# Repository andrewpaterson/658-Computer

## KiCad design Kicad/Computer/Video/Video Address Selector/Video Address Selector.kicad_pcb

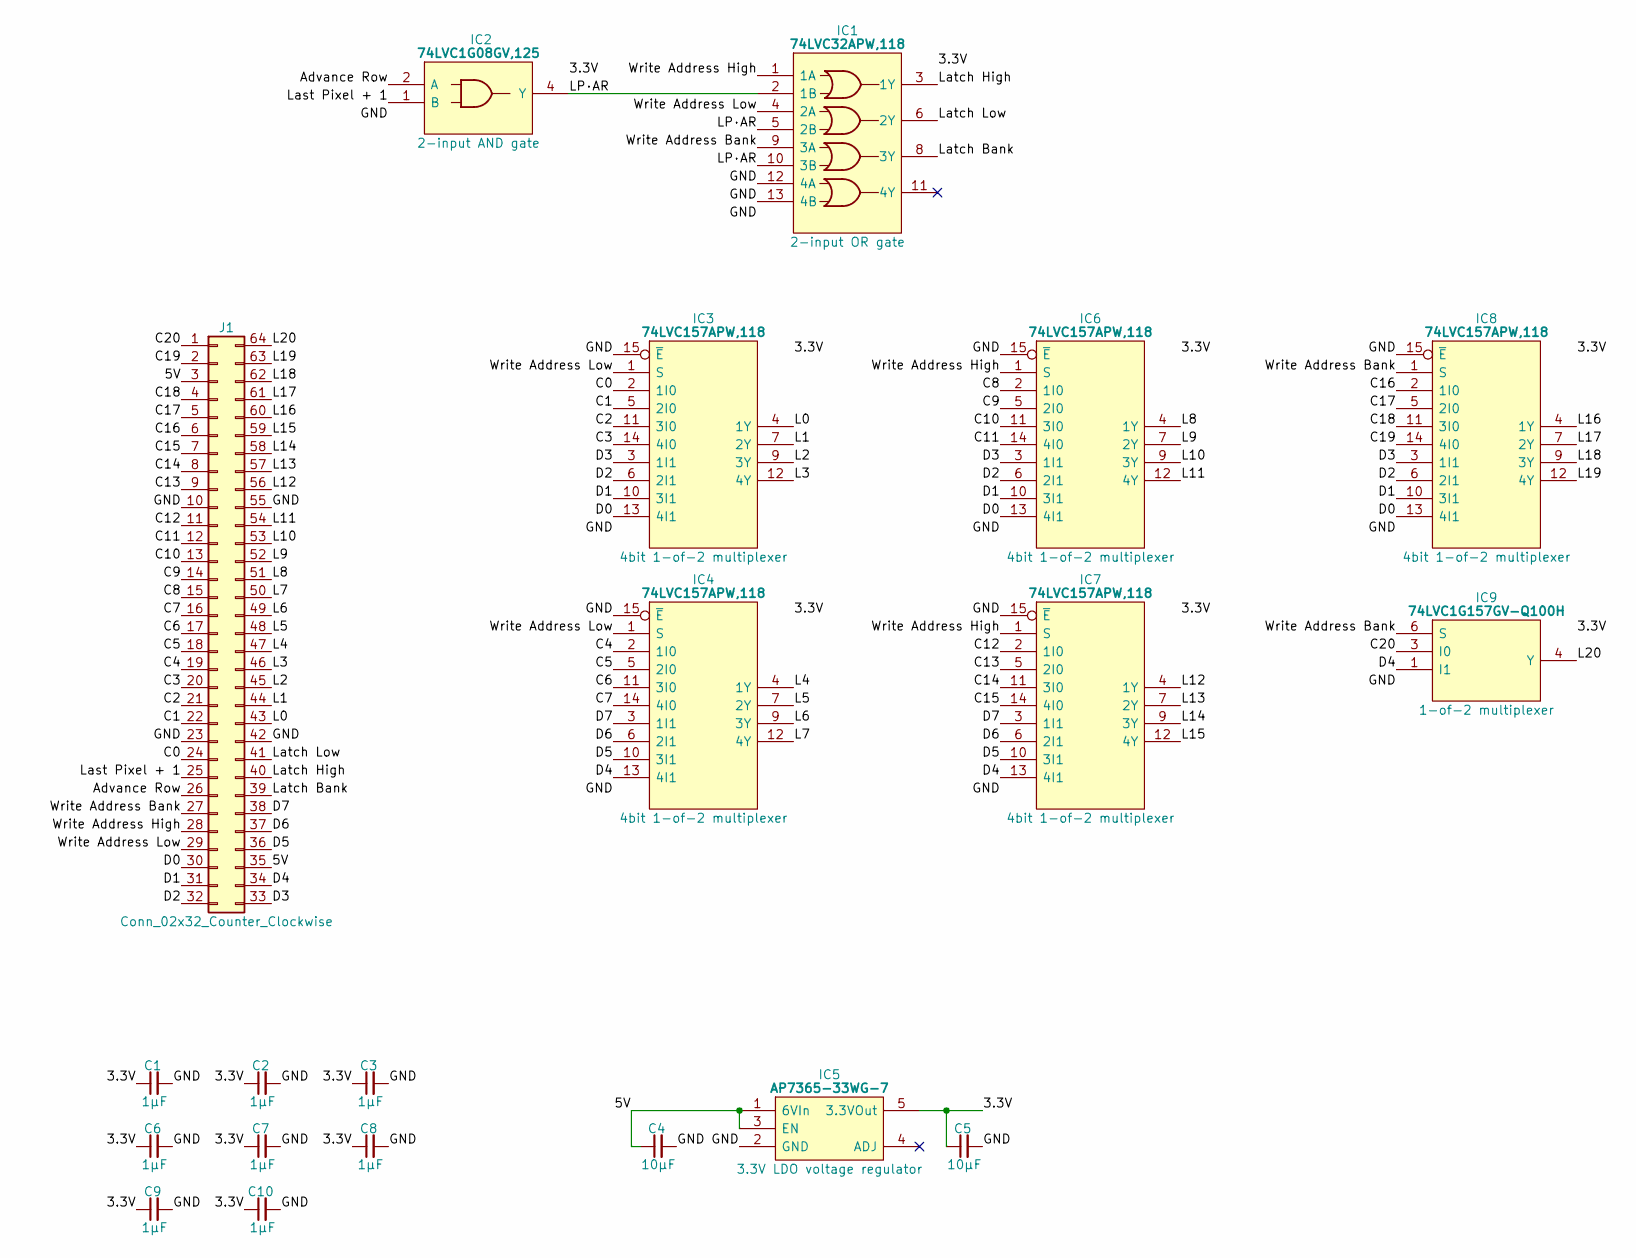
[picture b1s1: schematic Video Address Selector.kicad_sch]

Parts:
C1, C2, C3, C6, C7, C8, C9, C10: 1μF; C_0805
C4, C5: 10µF; C_0805
IC1: 74LVC32APW,118; SOP65P640X110-14N; Manufacturer_Part_Number 74LVC32APW,118; Mouser Part Number 771-74LVC32APW-T
IC2: 74LVC1G08GV,125; SOT95P275X110-5N; Manufacturer_Part_Number 74LVC1G08GV,125; Mouser Part Number 771-74LVC1G08GV
IC3, IC4, IC6, IC7, IC8: 74LVC157APW,118; SOP65P640X110-16N; Mouser Part Number 771-74LVC157APW-T
IC5: AP7365-33WG-7; SOT95P285X130-5N; Manufacturer_Part_Number AP7365-33WG-7; Mouser Part Number 621-AP7365-33WG-7
IC9: 74LVC1G157GV-Q100H; SOT95P275X110-6N; Manufacturer_Part_Number 74LVC1G157GV-Q100H; Mouser Part Number 771-74LVC1G157GVQ100
J1: Conn_02x32_Counter_Clockwise; DIP-64_Board_W15.24mm

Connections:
/3.3V: C1.1, C2.1, C3.1, C5.1, C6.1, C7.1, C8.1, C9.1, C10.1, IC1.14 (3V), IC2.5 (3V), IC3.16 (3V), IC4.16 (3V), IC5.5 (3.3VOut), IC6.16 (3V), IC7.16 (3V), IC8.16 (3V), IC9.5 (3V)
/5V: C4.1, IC5.1 (6VIn), IC5.3 (EN), J1.3, J1.35
/Advance Row: IC2.2 (A), J1.26
/C0: IC3.2 (1I0), J1.24
/C1: IC3.5 (2I0), J1.22
/C2: IC3.11 (3I0), J1.21
/C3: IC3.14 (4I0), J1.20
/C4: IC4.2 (1I0), J1.19
/C5: IC4.5 (2I0), J1.18
/C6: IC4.11 (3I0), J1.17
/C7: IC4.14 (4I0), J1.16
/C8: IC6.2 (1I0), J1.15
/C9: IC6.5 (2I0), J1.14
/C10: IC6.11 (3I0), J1.13
/C11: IC6.14 (4I0), J1.12
/C12: IC7.2 (1I0), J1.11
/C13: IC7.5 (2I0), J1.9
/C14: IC7.11 (3I0), J1.8
/C15: IC7.14 (4I0), J1.7
/C16: IC8.2 (1I0), J1.6
/C17: IC8.5 (2I0), J1.5
/C18: IC8.11 (3I0), J1.4
/C19: IC8.14 (4I0), J1.2
/C20: IC9.3 (I0), J1.1
/D0: IC3.13 (4I1), IC6.13 (4I1), IC8.13 (4I1), J1.30
/D1: IC3.10 (3I1), IC6.10 (3I1), IC8.10 (3I1), J1.31
/D2: IC3.6 (2I1), IC6.6 (2I1), IC8.6 (2I1), J1.32
/D3: IC3.3 (1I1), IC6.3 (1I1), IC8.3 (1I1), J1.33
/D4: IC4.13 (4I1), IC7.13 (4I1), IC9.1 (I1), J1.34
/D5: IC4.10 (3I1), IC7.10 (3I1), J1.36
/D6: IC4.6 (2I1), IC7.6 (2I1), J1.37
/D7: IC4.3 (1I1), IC7.3 (1I1), J1.38
/GND: C1.2, C2.2, C3.2, C4.2, C5.2, C6.2, C7.2, C8.2, C9.2, C10.2, IC1.7 (GND), IC1.12 (4A), IC1.13 (4B), IC2.3 (GND), IC3.8 (GND), IC3.15 (~E), IC4.8 (GND), IC4.15 (~E), IC5.2 (GND), IC6.8 (GND), IC6.15 (~E), IC7.8 (GND), IC7.15 (~E), IC8.8 (GND), IC8.15 (~E), IC9.2 (GND), J1.10, J1.23, J1.42, J1.55
/L0: IC3.4 (1Y), J1.43
/L1: IC3.7 (2Y), J1.44
/L2: IC3.9 (3Y), J1.45
/L3: IC3.12 (4Y), J1.46
/L4: IC4.4 (1Y), J1.47
/L5: IC4.7 (2Y), J1.48
/L6: IC4.9 (3Y), J1.49
/L7: IC4.12 (4Y), J1.50
/L8: IC6.4 (1Y), J1.51
/L9: IC6.7 (2Y), J1.52
/L10: IC6.9 (3Y), J1.53
/L11: IC6.12 (4Y), J1.54
/L12: IC7.4 (1Y), J1.56
/L13: IC7.7 (2Y), J1.57
/L14: IC7.9 (3Y), J1.58
/L15: IC7.12 (4Y), J1.59
/L16: IC8.4 (1Y), J1.60
/L17: IC8.7 (2Y), J1.61
/L18: IC8.9 (3Y), J1.62
/L19: IC8.12 (4Y), J1.63
/L20: IC9.4 (Y), J1.64
/LP·AR: IC1.2 (1B), IC1.5 (2B), IC1.10 (3B), IC2.4 (Y)
/Last Pixel + 1: IC2.1 (B), J1.25
/Latch Bank: IC1.8 (3Y), J1.39
/Latch High: IC1.3 (1Y), J1.40
/Latch Low: IC1.6 (2Y), J1.41
/Write Address Bank: IC1.9 (3A), IC8.1 (S), IC9.6 (S), J1.27
/Write Address High: IC1.1 (1A), IC6.1 (S), IC7.1 (S), J1.28
/Write Address Low: IC1.4 (2A), IC3.1 (S), IC4.1 (S), J1.29

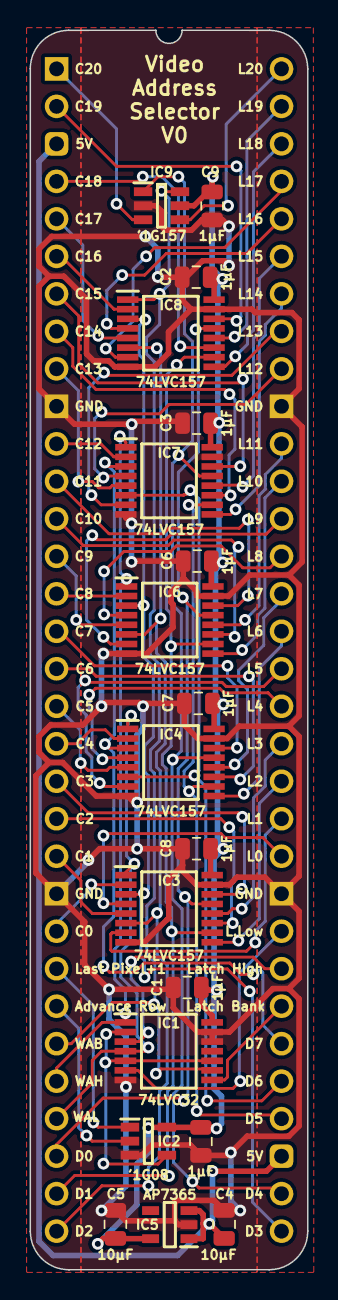
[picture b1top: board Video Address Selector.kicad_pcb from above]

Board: 2 copper layers, 18.8 x 84.0 mm, 20 parts (0 on the bottom side), 62 nets.

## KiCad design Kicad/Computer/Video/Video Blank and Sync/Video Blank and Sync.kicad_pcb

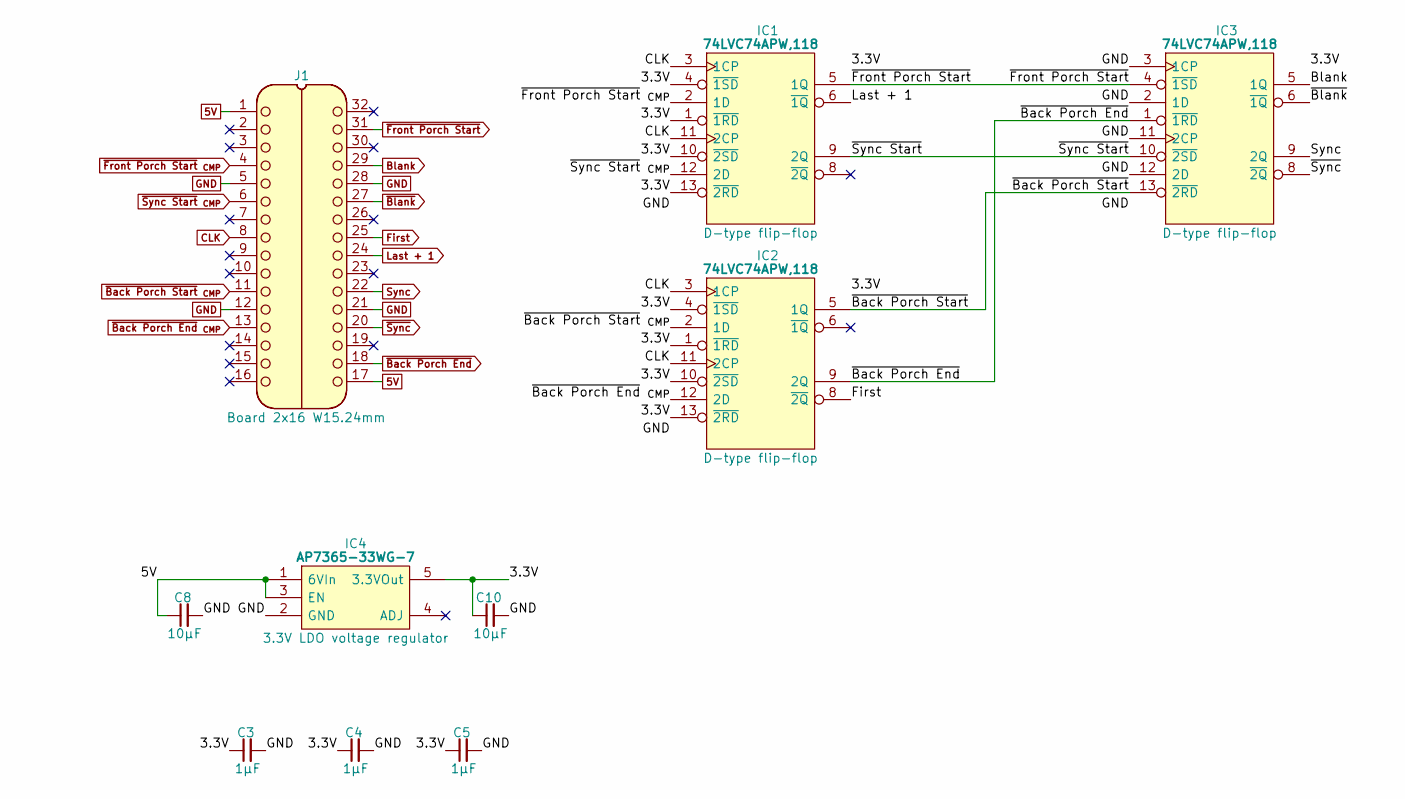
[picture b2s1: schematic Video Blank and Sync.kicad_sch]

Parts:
C3, C4, C5: 1μF; C_0805
C8, C10: 10µF; C_0805
IC1, IC2, IC3: 74LVC74APW,118; SOP65P640X110-14N; Mouser Part Number 771-74LVC74APW-T
IC4: AP7365-33WG-7; SOT95P285X130-5N; Manufacturer_Part_Number AP7365-33WG-7; Mouser Part Number 621-AP7365-33WG-7
J1: Board 2x16 W15.24mm; DIP-32_Board_W15.24mm

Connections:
5V: C8.1, IC4.1 (6VIn), IC4.3 (EN), J1.1, J1.17
/3.3V: C3.1, C4.1, C5.1, C10.1, IC1.1 (~1RD), IC1.4 (~1SD), IC1.10 (~2SD), IC1.13 (~2RD), IC1.14 (3V), IC2.1 (~1RD), IC2.4 (~1SD), IC2.10 (~2SD), IC2.13 (~2RD), IC2.14 (3V), IC3.14 (3V), IC4.5 (3.3VOut)
/~Back Porch Start: IC2.5 (1Q), IC3.13 (~2RD)
/~Sync Start: IC1.9 (2Q), IC3.10 (~2SD)
Blank: IC3.5 (1Q), J1.29
CLK: IC1.3 (1CP), IC1.11 (2CP), IC2.3 (1CP), IC2.11 (2CP), J1.8
First: IC2.8 (~2Q), J1.25
GND: C3.2, C4.2, C5.2, C8.2, C10.2, IC1.7 (GND), IC2.7 (GND), IC3.2 (1D), IC3.3 (1CP), IC3.7 (GND), IC3.11 (2CP), IC3.12 (2D), IC4.2 (GND), J1.5, J1.12, J1.21, J1.28
Last + 1: IC1.6 (~1Q), J1.24
Sync: IC3.9 (2Q), J1.22
~Back Porch End: IC2.9 (2Q), IC3.1 (~1RD), J1.18
~Back Porch End _{CMP}: IC2.12 (2D), J1.13
~Back Porch Start _{CMP}: IC2.2 (1D), J1.11
~Blank: IC3.6 (~1Q), J1.27
~Front Porch Start: IC1.5 (1Q), IC3.4 (~1SD), J1.31
~Front Porch Start _{CMP}: IC1.2 (1D), J1.4
~Sync Start _{CMP}: IC1.12 (2D), J1.6
~Sync: IC3.8 (~2Q), J1.20

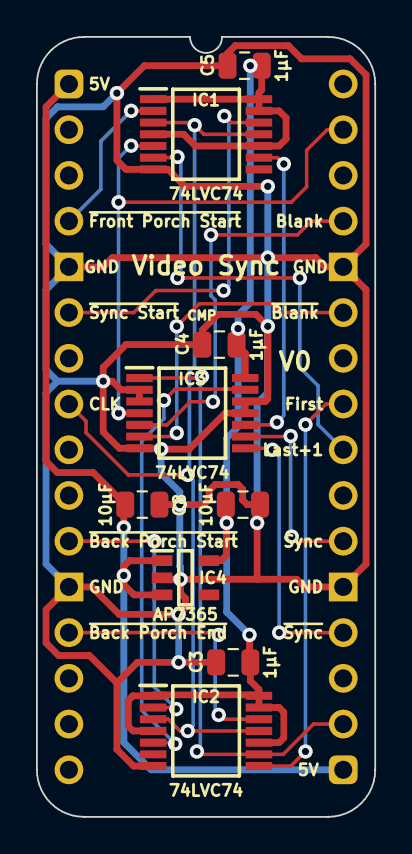
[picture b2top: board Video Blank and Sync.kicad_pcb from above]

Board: 2 copper layers, 18.8 x 43.3 mm, 10 parts (0 on the bottom side), 18 nets.

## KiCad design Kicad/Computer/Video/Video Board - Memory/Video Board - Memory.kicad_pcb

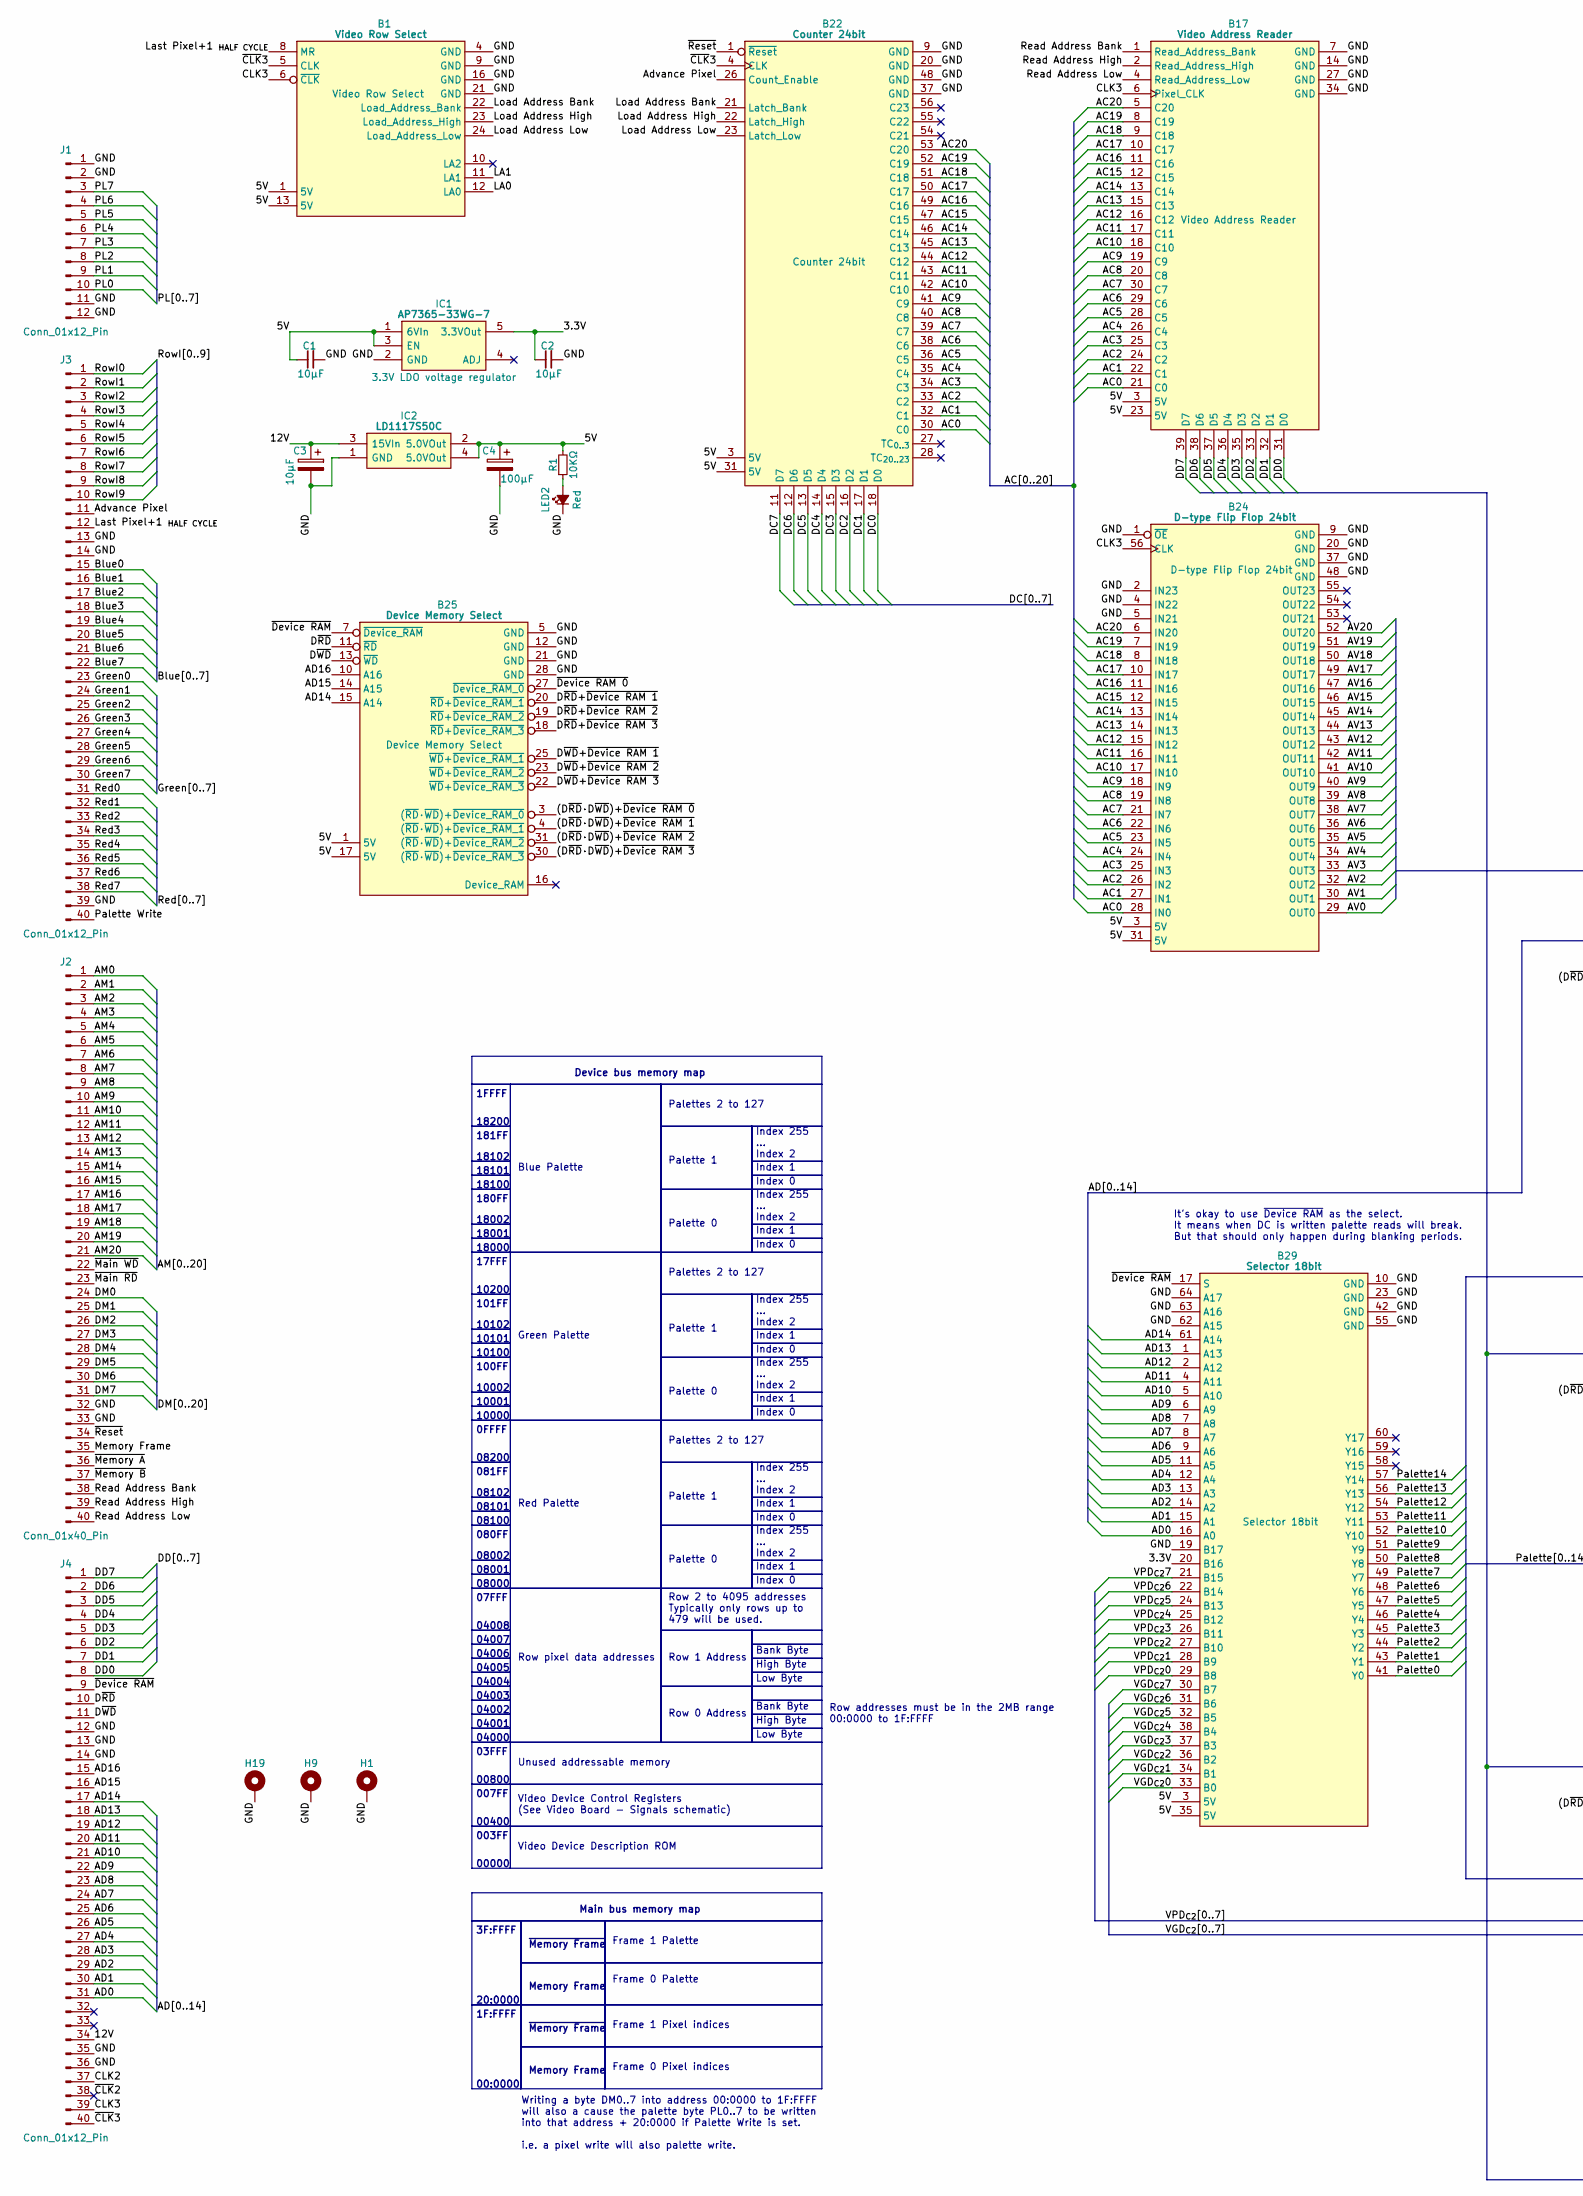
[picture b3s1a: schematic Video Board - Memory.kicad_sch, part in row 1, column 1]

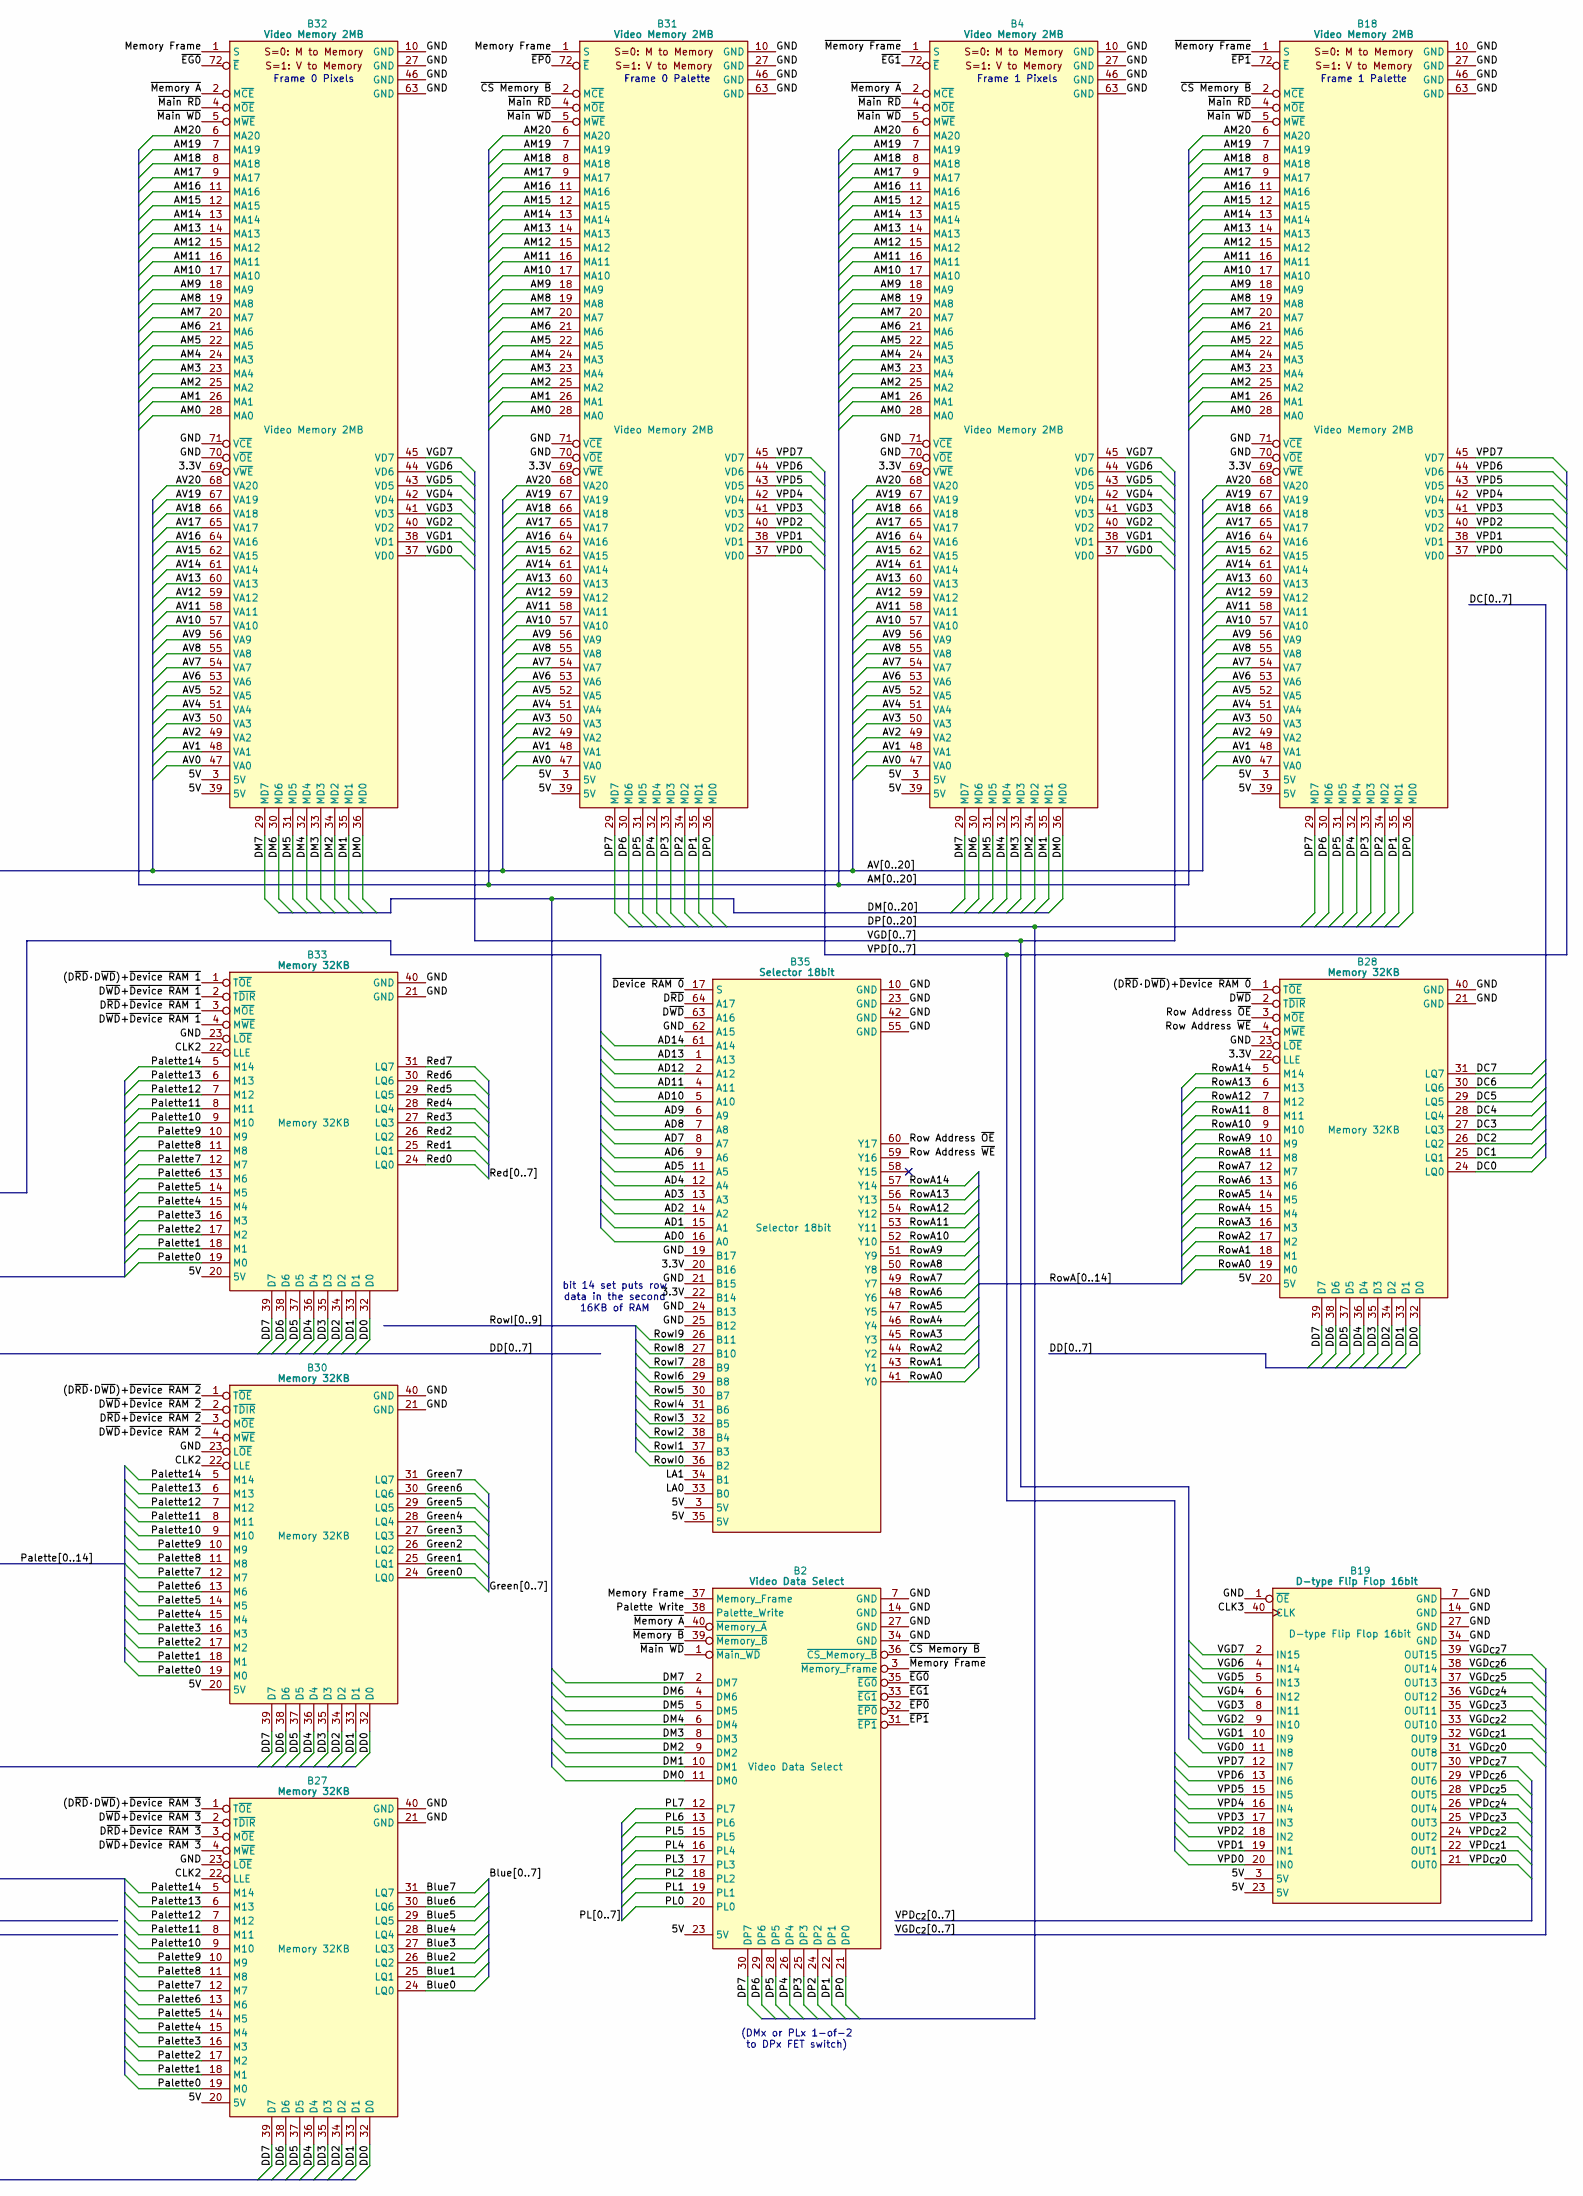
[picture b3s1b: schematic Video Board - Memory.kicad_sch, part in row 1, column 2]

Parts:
B1: Video Row Select; HCP65_Video_Row_Select
B2: Video Data Select; HCP65_Video_Data_Select
B4, B18, B31, B32: Video Memory 2MB; HCP65_Video_Memory_2MB
B17: Video Address Reader; HCP65_Video_Address_Reader
B19: D-type Flip Flop 16bit; HCP65_D_Flip_Flop_16bit
B22: Counter 24bit; HCP65_Counter_24bit
B24: D-type Flip Flop 24bit; HCP65_D_Flip_Flop_24bit
B25: Device Memory Select; HCP65_Video_Device_RAM_Select
B27, B28, B30, B33: Memory 32KB; HCP65_Memory_32KB_With_Latch
B29, B35: Selector 18bit; HCP65_Selector_18bit
C1, C2: 10µF; C_0805
C3: 10μF; CP_Radial_D4.0mm_P2.00mm
C4: 100μF; CP_Radial_D4.0mm_P2.00mm
H1, H9, H19: MountingHole_Pad; HCP65_MountingHole_M3_
IC1: AP7365-33WG-7; SOT95P285X130-5N; Manufacturer_Part_Number AP7365-33WG-7; Mouser Part Number 621-AP7365-33WG-7
IC2: LD1117S50C; LD1117S33C; Manufacturer_Part_Number LD1117S50C
J1: Conn_01x12_Pin; PinSocket_2x06_P2.54mm_Vertical
J2: Conn_01x40_Pin; PinSocket_2x20_P2.54mm_Vertical
J3, J4: Conn_01x12_Pin; PinSocket_2x20_P2.54mm_Vertical
LED2: Red; LED_D5.0mm
R1: 10KΩ; R_0805

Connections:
/3.3V: B4.69 (V~WE), B18.69 (V~WE), B28.22 (LLE), B29.20 (B16), B31.69 (V~WE), B32.69 (V~WE), B35.20 (B16), B35.22 (B14), C2.1, IC1.5 (3.3VOut)
/5V: B1.1 (5V), B1.13 (5V), B2.23 (5V), B4.3 (5V), B4.39 (5V), B17.3 (5V), B17.23 (5V), B18.3 (5V), B18.39 (5V), B19.3 (5V), B19.23 (5V), B22.3 (5V), B22.31 (5V), B24.3 (5V), B24.31 (5V), B25.1 (5V), B25.17 (5V), B27.20 (5V), B28.20 (5V), B29.3 (5V), B29.35 (5V), B30.20 (5V), B31.3 (5V), B31.39 (5V), B32.3 (5V), B32.39 (5V), B33.20 (5V), B35.3 (5V), B35.35 (5V), C1.1, C4.1, IC1.1 (6VIn), IC1.3 (EN), IC2.2 (5.0VOut), IC2.4 (5.0VOut), R1.2
/12V: C3.1, IC2.3 (15VIn), J4.34
/(D~RD·D~WD)+~Device RAM 0: B25.3 ((~RD·~WD)+~Device_RAM_0), B28.1 (T~OE)
/(D~RD·D~WD)+~Device RAM 1: B25.4 ((~RD·~WD)+~Device_RAM_1), B33.1 (T~OE)
/(D~RD·D~WD)+~Device RAM 2: B25.31 ((~RD·~WD)+~Device_RAM_2), B30.1 (T~OE)
/(D~RD·D~WD)+~Device RAM 3: B25.30 ((~RD·~WD)+~Device_RAM_3), B27.1 (T~OE)
/AC0: B17.21 (C0), B22.30 (C0), B24.28 (IN0)
/AC1: B17.22 (C1), B22.32 (C1), B24.27 (IN1)
/AC2: B17.24 (C2), B22.33 (C2), B24.26 (IN2)
/AC3: B17.25 (C3), B22.34 (C3), B24.25 (IN3)
/AC4: B17.26 (C4), B22.35 (C4), B24.24 (IN4)
/AC5: B17.28 (C5), B22.36 (C5), B24.23 (IN5)
/AC6: B17.29 (C6), B22.38 (C6), B24.22 (IN6)
/AC7: B17.30 (C7), B22.39 (C7), B24.21 (IN7)
/AC8: B17.20 (C8), B22.40 (C8), B24.19 (IN8)
/AC9: B17.19 (C9), B22.41 (C9), B24.18 (IN9)
/AC10: B17.18 (C10), B22.42 (C10), B24.17 (IN10)
/AC11: B17.17 (C11), B22.43 (C11), B24.16 (IN11)
/AC12: B17.16 (C12), B22.44 (C12), B24.15 (IN12)
/AC13: B17.15 (C13), B22.45 (C13), B24.14 (IN13)
/AC14: B17.13 (C14), B22.46 (C14), B24.13 (IN14)
/AC15: B17.12 (C15), B22.47 (C15), B24.12 (IN15)
/AC16: B17.11 (C16), B22.49 (C16), B24.11 (IN16)
/AC17: B17.10 (C17), B22.50 (C17), B24.10 (IN17)
/AC18: B17.9 (C18), B22.51 (C18), B24.8 (IN18)
/AC19: B17.8 (C19), B22.52 (C19), B24.7 (IN19)
/AC20: B17.5 (C20), B22.53 (C20), B24.6 (IN20)
/AD0: B29.16 (A0), B35.16 (A0), J4.31
/AD1: B29.15 (A1), B35.15 (A1), J4.30
/AD2: B29.14 (A2), B35.14 (A2), J4.29
/AD3: B29.13 (A3), B35.13 (A3), J4.28
/AD4: B29.12 (A4), B35.12 (A4), J4.27
/AD5: B29.11 (A5), B35.11 (A5), J4.26
/AD6: B29.9 (A6), B35.9 (A6), J4.25
/AD7: B29.8 (A7), B35.8 (A7), J4.24
/AD8: B29.7 (A8), B35.7 (A8), J4.23
/AD9: B29.6 (A9), B35.6 (A9), J4.22
/AD10: B29.5 (A10), B35.5 (A10), J4.21
/AD11: B29.4 (A11), B35.4 (A11), J4.20
/AD12: B29.2 (A12), B35.2 (A12), J4.19
/AD13: B29.1 (A13), B35.1 (A13), J4.18
/AD14: B25.15 (A14), B29.61 (A14), B35.61 (A14), J4.17
/AD15: B25.14 (A15), J4.16
/AD16: B25.10 (A16), J4.15
/AM0: B4.28 (MA0), B18.28 (MA0), B31.28 (MA0), B32.28 (MA0), J2.1
/AM1: B4.26 (MA1), B18.26 (MA1), B31.26 (MA1), B32.26 (MA1), J2.2
/AM2: B4.25 (MA2), B18.25 (MA2), B31.25 (MA2), B32.25 (MA2), J2.3
/AM3: B4.23 (MA4), B18.23 (MA4), B31.23 (MA4), B32.23 (MA4), J2.4
/AM4: B4.24 (MA3), B18.24 (MA3), B31.24 (MA3), B32.24 (MA3), J2.5
/AM5: B4.22 (MA5), B18.22 (MA5), B31.22 (MA5), B32.22 (MA5), J2.6
/AM6: B4.21 (MA6), B18.21 (MA6), B31.21 (MA6), B32.21 (MA6), J2.7
/AM7: B4.20 (MA7), B18.20 (MA7), B31.20 (MA7), B32.20 (MA7), J2.8
/AM8: B4.19 (MA8), B18.19 (MA8), B31.19 (MA8), B32.19 (MA8), J2.9
/AM9: B4.18 (MA9), B18.18 (MA9), B31.18 (MA9), B32.18 (MA9), J2.10
/AM10: B4.17 (MA10), B18.17 (MA10), B31.17 (MA10), B32.17 (MA10), J2.11
/AM11: B4.16 (MA11), B18.16 (MA11), B31.16 (MA11), B32.16 (MA11), J2.12
/AM12: B4.15 (MA12), B18.15 (MA12), B31.15 (MA12), B32.15 (MA12), J2.13
/AM13: B4.14 (MA13), B18.14 (MA13), B31.14 (MA13), B32.14 (MA13), J2.14
/AM14: B4.13 (MA14), B18.13 (MA14), B31.13 (MA14), B32.13 (MA14), J2.15
/AM15: B4.12 (MA15), B18.12 (MA15), B31.12 (MA15), B32.12 (MA15), J2.16
/AM16: B4.11 (MA16), B18.11 (MA16), B31.11 (MA16), B32.11 (MA16), J2.17
/AM17: B4.9 (MA17), B18.9 (MA17), B31.9 (MA17), B32.9 (MA17), J2.18
/AM18: B4.8 (MA18), B18.8 (MA18), B31.8 (MA18), B32.8 (MA18), J2.19
/AM19: B4.7 (MA19), B18.7 (MA19), B31.7 (MA19), B32.7 (MA19), J2.20
/AM20: B4.6 (MA20), B18.6 (MA20), B31.6 (MA20), B32.6 (MA20), J2.21
/AV0: B4.47 (VA0), B18.47 (VA0), B24.29 (OUT0), B31.47 (VA0), B32.47 (VA0)
/AV1: B4.48 (VA1), B18.48 (VA1), B24.30 (OUT1), B31.48 (VA1), B32.48 (VA1)
/AV2: B4.49 (VA2), B18.49 (VA2), B24.32 (OUT2), B31.49 (VA2), B32.49 (VA2)
/AV3: B4.50 (VA3), B18.50 (VA3), B24.33 (OUT3), B31.50 (VA3), B32.50 (VA3)
/AV4: B4.51 (VA4), B18.51 (VA4), B24.34 (OUT4), B31.51 (VA4), B32.51 (VA4)
/AV5: B4.52 (VA5), B18.52 (VA5), B24.35 (OUT5), B31.52 (VA5), B32.52 (VA5)
/AV6: B4.53 (VA6), B18.53 (VA6), B24.36 (OUT6), B31.53 (VA6), B32.53 (VA6)
/AV7: B4.54 (VA7), B18.54 (VA7), B24.38 (OUT7), B31.54 (VA7), B32.54 (VA7)
/AV8: B4.55 (VA8), B18.55 (VA8), B24.39 (OUT8), B31.55 (VA8), B32.55 (VA8)
/AV9: B4.56 (VA9), B18.56 (VA9), B24.40 (OUT9), B31.56 (VA9), B32.56 (VA9)
/AV10: B4.57 (VA10), B18.57 (VA10), B24.41 (OUT10), B31.57 (VA10), B32.57 (VA10)
/AV11: B4.58 (VA11), B18.58 (VA11), B24.42 (OUT11), B31.58 (VA11), B32.58 (VA11)
/AV12: B4.59 (VA12), B18.59 (VA12), B24.43 (OUT12), B31.59 (VA12), B32.59 (VA12)
/AV13: B4.60 (VA13), B18.60 (VA13), B24.44 (OUT13), B31.60 (VA13), B32.60 (VA13)
/AV14: B4.61 (VA14), B18.61 (VA14), B24.45 (OUT14), B31.61 (VA14), B32.61 (VA14)
/AV15: B4.62 (VA15), B18.62 (VA15), B24.46 (OUT15), B31.62 (VA15), B32.62 (VA15)
/AV16: B4.64 (VA16), B18.64 (VA16), B24.47 (OUT16), B31.64 (VA16), B32.64 (VA16)
/AV17: B4.65 (VA17), B18.65 (VA17), B24.49 (OUT17), B31.65 (VA17), B32.65 (VA17)
/AV18: B4.66 (VA18), B18.66 (VA18), B24.50 (OUT18), B31.66 (VA18), B32.66 (VA18)
/AV19: B4.67 (VA19), B18.67 (VA19), B24.51 (OUT19), B31.67 (VA19), B32.67 (VA19)
/AV20: B4.68 (VA20), B18.68 (VA20), B24.52 (OUT20), B31.68 (VA20), B32.68 (VA20)
/Advance Pixel: B22.26 (Count_Enable), J3.11
/Blue0: B27.24 (LQ0), J3.15
/Blue1: B27.25 (LQ1), J3.16
/Blue2: B27.26 (LQ2), J3.17
/Blue3: B27.27 (LQ3), J3.18
/Blue4: B27.28 (LQ4), J3.19
/Blue5: B27.29 (LQ5), J3.20
/Blue6: B27.30 (LQ6), J3.21
/Blue7: B27.31 (LQ7), J3.22
/CLK2: B27.22 (LLE), B30.22 (LLE), B33.22 (LLE), J4.37
/CLK3: B1.6 (~CLK), B17.6 (Pixel_CLK), B19.40 (CLK), B24.56 (CLK), J4.39
/DC0: B22.18 (D0), B28.24 (LQ0)
/DC1: B22.17 (D1), B28.25 (LQ1)
/DC2: B22.16 (D2), B28.26 (LQ2)
/DC3: B22.15 (D3), B28.27 (LQ3)
/DC4: B22.14 (D4), B28.28 (LQ4)
/DC5: B22.13 (D5), B28.29 (LQ5)
/DC6: B22.12 (D6), B28.30 (LQ6)
/DC7: B22.11 (D7), B28.31 (LQ7)
/DD0: B17.31 (D0), B27.32 (D0), B28.32 (D0), B30.32 (D0), B33.32 (D0), J4.8
/DD1: B17.32 (D1), B27.33 (D1), B28.33 (D1), B30.33 (D1), B33.33 (D1), J4.7
/DD2: B17.33 (D2), B27.34 (D2), B28.34 (D2), B30.34 (D2), B33.34 (D2), J4.6
/DD3: B17.35 (D3), B27.35 (D3), B28.35 (D3), B30.35 (D3), B33.35 (D3), J4.5
/DD4: B17.36 (D4), B27.36 (D4), B28.36 (D4), B30.36 (D4), B33.36 (D4), J4.4
/DD5: B17.37 (D5), B27.37 (D5), B28.37 (D5), B30.37 (D5), B33.37 (D5), J4.3
/DD6: B17.38 (D6), B27.38 (D6), B28.38 (D6), B30.38 (D6), B33.38 (D6), J4.2
/DD7: B17.39 (D7), B27.39 (D7), B28.39 (D7), B30.39 (D7), B33.39 (D7), J4.1
/DM0: B2.11 (DM0), B4.36 (MD0), B32.36 (MD0), J2.24
/DM1: B2.10 (DM1), B4.35 (MD1), B32.35 (MD1), J2.25
/DM2: B2.9 (DM2), B4.34 (MD2), B32.34 (MD2), J2.26
/DM3: B2.8 (DM3), B4.33 (MD3), B32.33 (MD3), J2.27
/DM4: B2.6 (DM4), B4.32 (MD4), B32.32 (MD4), J2.28
/DM5: B2.5 (DM5), B4.31 (MD5), B32.31 (MD5), J2.29
/DM6: B2.4 (DM6), B4.30 (MD6), B32.30 (MD6), J2.30
/DM7: B2.2 (DM7), B4.29 (MD7), B32.29 (MD7), J2.31
/DP0: B2.21 (DP0), B18.36 (MD0), B31.36 (MD0)
/DP1: B2.22 (DP1), B18.35 (MD1), B31.35 (MD1)
/DP2: B2.24 (DP2), B18.34 (MD2), B31.34 (MD2)
/DP3: B2.25 (DP3), B18.33 (MD3), B31.33 (MD3)
/DP4: B2.26 (DP4), B18.32 (MD4), B31.32 (MD4)
/DP5: B2.28 (DP5), B18.31 (MD5), B31.31 (MD5)
/DP6: B2.29 (DP6), B18.30 (MD6), B31.30 (MD6)
/DP7: B2.30 (DP7), B18.29 (MD7), B31.29 (MD7)
/D~RD: B25.11 (~RD), B35.64 (A17), J4.10
/D~RD+~Device RAM 1: B25.20 (~RD+~Device_RAM_1), B33.3 (M~OE)
/D~RD+~Device RAM 2: B25.19 (~RD+~Device_RAM_2), B30.3 (M~OE)
/D~RD+~Device RAM 3: B25.18 (~RD+~Device_RAM_3), B27.3 (M~OE)
/D~WD: B25.13 (~WD), B28.2 (T~DIR), B35.63 (A16), J4.11
/D~WD+~Device RAM 1: B25.25 (~WD+~Device_RAM_1), B33.2 (T~DIR), B33.4 (M~WE)
/D~WD+~Device RAM 2: B25.23 (~WD+~Device_RAM_2), B30.2 (T~DIR), B30.4 (M~WE)
/D~WD+~Device RAM 3: B25.22 (~WD+~Device_RAM_3), B27.2 (T~DIR), B27.4 (M~WE)
/Green0: B30.24 (LQ0), J3.23
/Green1: B30.25 (LQ1), J3.24
/Green2: B30.26 (LQ2), J3.25
/Green3: B30.27 (LQ3), J3.26
/Green4: B30.28 (LQ4), J3.27
/Green5: B30.29 (LQ5), J3.28
/Green6: B30.30 (LQ6), J3.29
/Green7: B30.31 (LQ7), J3.30
/LA0: B1.12 (LA0), B35.33 (B0)
/LA1: B1.11 (LA1), B35.34 (B1)
/Last Pixel+1 _{HALF CYCLE}: B1.8 (MR), J3.12
/Load Address Bank: B1.22 (Load_Address_Bank), B22.21 (Latch_Bank)
/Load Address High: B1.23 (Load_Address_High), B22.22 (Latch_High)
/Load Address Low: B1.24 (Load_Address_Low), B22.23 (Latch_Low)
/Memory Frame: B2.37 (Memory_Frame), B31.1 (S), B32.1 (S), J2.35
/Palette0: B27.19 (M0), B29.41 (Y0), B30.19 (M0), B33.19 (M0)
/Palette1: B27.18 (M1), B29.43 (Y1), B30.18 (M1), B33.18 (M1)
/Palette2: B27.17 (M2), B29.44 (Y2), B30.17 (M2), B33.17 (M2)
/Palette3: B27.16 (M3), B29.45 (Y3), B30.16 (M3), B33.16 (M3)
/Palette4: B27.15 (M4), B29.46 (Y4), B30.15 (M4), B33.15 (M4)
/Palette5: B27.14 (M5), B29.47 (Y5), B30.14 (M5), B33.14 (M5)
/Palette6: B27.13 (M6), B29.48 (Y6), B30.13 (M6), B33.13 (M6)
/Palette7: B27.12 (M7), B29.49 (Y7), B30.12 (M7), B33.12 (M7)
/Palette8: B27.11 (M8), B29.50 (Y8), B30.11 (M8), B33.11 (M8)
/Palette9: B27.10 (M9), B29.51 (Y9), B30.10 (M9), B33.10 (M9)
/Palette10: B27.9 (M10), B29.52 (Y10), B30.9 (M10), B33.9 (M10)
/Palette11: B27.8 (M11), B29.53 (Y11), B30.8 (M11), B33.8 (M11)
/Palette12: B27.7 (M12), B29.54 (Y12), B30.7 (M12), B33.7 (M12)
/Palette13: B27.6 (M13), B29.56 (Y13), B30.6 (M13), B33.6 (M13)
/Palette14: B27.5 (M14), B29.57 (Y14), B30.5 (M14), B33.5 (M14)
/Palette Write: B2.38 (Palette_Write), J3.40
/Read Address Bank: B17.1 (Read_Address_Bank), J2.38
/Read Address High: B17.2 (Read_Address_High), J2.39
/Read Address Low: B17.4 (Read_Address_Low), J2.40
/Red0: B33.24 (LQ0), J3.31
/Red1: B33.25 (LQ1), J3.32
/Red2: B33.26 (LQ2), J3.33
/Red3: B33.27 (LQ3), J3.34
/Red4: B33.28 (LQ4), J3.35
/Red5: B33.29 (LQ5), J3.36
/Red6: B33.30 (LQ6), J3.37
/Red7: B33.31 (LQ7), J3.38
/Row Address ~OE: B28.3 (M~OE), B35.60 (Y17)
/Row Address ~WE: B28.4 (M~WE), B35.59 (Y16)
/RowA0: B28.19 (M0), B35.41 (Y0)
/RowA1: B28.18 (M1), B35.43 (Y1)
/RowA2: B28.17 (M2), B35.44 (Y2)
/RowA3: B28.16 (M3), B35.45 (Y3)
/RowA4: B28.15 (M4), B35.46 (Y4)
/RowA5: B28.14 (M5), B35.47 (Y5)
/RowA6: B28.13 (M6), B35.48 (Y6)
/RowA7: B28.12 (M7), B35.49 (Y7)
/RowA8: B28.11 (M8), B35.50 (Y8)
/RowA9: B28.10 (M9), B35.51 (Y9)
/RowA10: B28.9 (M10), B35.52 (Y10)
/RowA11: B28.8 (M11), B35.53 (Y11)
/RowA12: B28.7 (M12), B35.54 (Y12)
/RowA13: B28.6 (M13), B35.56 (Y13)
/RowA14: B28.5 (M14), B35.57 (Y14)
/RowI0: B35.36 (B2), J3.1
/RowI1: B35.37 (B3), J3.2
/RowI2: B35.38 (B4), J3.3
/RowI3: B35.32 (B5), J3.4
/RowI4: B35.31 (B6), J3.5
/RowI5: B35.30 (B7), J3.6
/RowI6: B35.29 (B8), J3.7
/RowI7: B35.28 (B9), J3.8
/RowI8: B35.27 (B10), J3.9
/RowI9: B35.26 (B11), J3.10
/VGD0: B4.37 (VD0), B19.11 (IN8), B32.37 (VD0)
/VGD1: B4.38 (VD1), B19.10 (IN9), B32.38 (VD1)
/VGD2: B4.40 (VD2), B19.9 (IN10), B32.40 (VD2)
/VGD3: B4.41 (VD3), B19.8 (IN11), B32.41 (VD3)
/VGD4: B4.42 (VD4), B19.6 (IN12), B32.42 (VD4)
/VGD5: B4.43 (VD5), B19.5 (IN13), B32.43 (VD5)
/VGD6: B4.44 (VD6), B19.4 (IN14), B32.44 (VD6)
/VGD7: B4.45 (VD7), B19.2 (IN15), B32.45 (VD7)
/VGD_{C2}0: B19.31 (OUT8), B29.33 (B0)
/VGD_{C2}1: B19.32 (OUT9), B29.34 (B1)
/VGD_{C2}2: B19.33 (OUT10), B29.36 (B2)
/VGD_{C2}3: B19.35 (OUT11), B29.37 (B3)
/VGD_{C2}4: B19.36 (OUT12), B29.38 (B4)
/VGD_{C2}5: B19.37 (OUT13), B29.32 (B5)
/VGD_{C2}6: B19.38 (OUT14), B29.31 (B6)
/VGD_{C2}7: B19.39 (OUT15), B29.30 (B7)
/VPD0: B18.37 (VD0), B19.20 (IN0), B31.37 (VD0)
/VPD1: B18.38 (VD1), B19.19 (IN1), B31.38 (VD1)
/VPD2: B18.40 (VD2), B19.18 (IN2), B31.40 (VD2)
/VPD3: B18.41 (VD3), B19.17 (IN3), B31.41 (VD3)
/VPD4: B18.42 (VD4), B19.16 (IN4), B31.42 (VD4)
/VPD5: B18.43 (VD5), B19.15 (IN5), B31.43 (VD5)
/VPD6: B18.44 (VD6), B19.13 (IN6), B31.44 (VD6)
/VPD7: B18.45 (VD7), B19.12 (IN7), B31.45 (VD7)
/VPD_{C2}0: B19.21 (OUT0), B29.29 (B8)
/VPD_{C2}1: B19.22 (OUT1), B29.28 (B9)
/VPD_{C2}2: B19.24 (OUT2), B29.27 (B10)
/VPD_{C2}3: B19.25 (OUT3), B29.26 (B11)
/VPD_{C2}4: B19.26 (OUT4), B29.25 (B12)
/VPD_{C2}5: B19.28 (OUT5), B29.24 (B13)
/VPD_{C2}6: B19.29 (OUT6), B29.22 (B14)
/VPD_{C2}7: B19.30 (OUT7), B29.21 (B15)
/~CLK2: J4.38
/~CLK3: B1.5 (CLK), B22.4 (CLK), J4.40
/~CS Memory B: B2.36 (~CS_Memory_B), B18.2 (M~CE), B31.2 (M~CE)
/~Device RAM 0: B25.27 (~Device_RAM_0), B35.17 (S)
/~Device RAM: B25.7 (~Device_RAM), B29.17 (S), J4.9
/~EG0: B2.35 (~EG0), B32.72 (~E)
/~EG1: B2.33 (~EG1), B4.72 (~E)
/~EP0: B2.32 (~EP0), B31.72 (~E)
/~EP1: B2.31 (~EP1), B18.72 (~E)
/~Main RD: B4.4 (M~OE), B18.4 (M~OE), B31.4 (M~OE), B32.4 (M~OE), J2.23
/~Main WD: B2.1 (~Main_WD), B4.5 (M~WE), B18.5 (M~WE), B31.5 (M~WE), B32.5 (M~WE), J2.22
/~Memory A: B2.40 (~Memory_A), B4.2 (M~CE), B32.2 (M~CE), J2.36
/~Memory B: B2.39 (~Memory_B), J2.37
/~Memory Frame: B2.3 (~Memory_Frame), B4.1 (S), B18.1 (S)
/~Reset: B22.1 (~Reset), J2.34
unnamed: LED2.2 (A), R1.1

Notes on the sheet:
181FF
18001
Palettes 2 to 127
Index 1
10000
Palette 0
10001
03FFF
Index 0
(DMx or PLx 1-of-2 to DPx FET switch)
00400
18002
08002
Video Device Control Registers (See Video Board - Signals schematic)
Memory Frame
08101
Frame 1 Palette
bit 14 set puts row data in the second 16KB of RAM
It's okay to use ~{Device RAM} as the select. It means when DC is written palette reads will break. But that should only happen during blanking periods.
180FF
Main bus memory map
04003
Frame 0 Palette
Palette 1
18101
04001
3F:FFFF
04008
Frame 1 Pixel indices
Row 0 Address
Frame 0 Pixel indices
Device bus memory map
Green Palette
1F:FFFF
101FF
Row addresses must be in the 2MB range 00:0000 to 1F:FFFF
Index 255 ... Index 2
Unused addressable memory
100FF
High Byte

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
